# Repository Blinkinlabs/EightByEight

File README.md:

# EightByEight Blinky Badge

EightByEight Blinky Badge, Copyright 2016 Blinkinlabs, LLC

See the ['Getting Started Guide'](https://github.com/Blinkinlabs/EightByEight/blob/master/documentation/Getting%20started%20guide.pdf) in documentation/ to learn about the badge.

Arduino examples are located in examples/.

# License

The hardware design is released under the CERN OHL v.1.2

The firmware and bootloader are released under the MIT license

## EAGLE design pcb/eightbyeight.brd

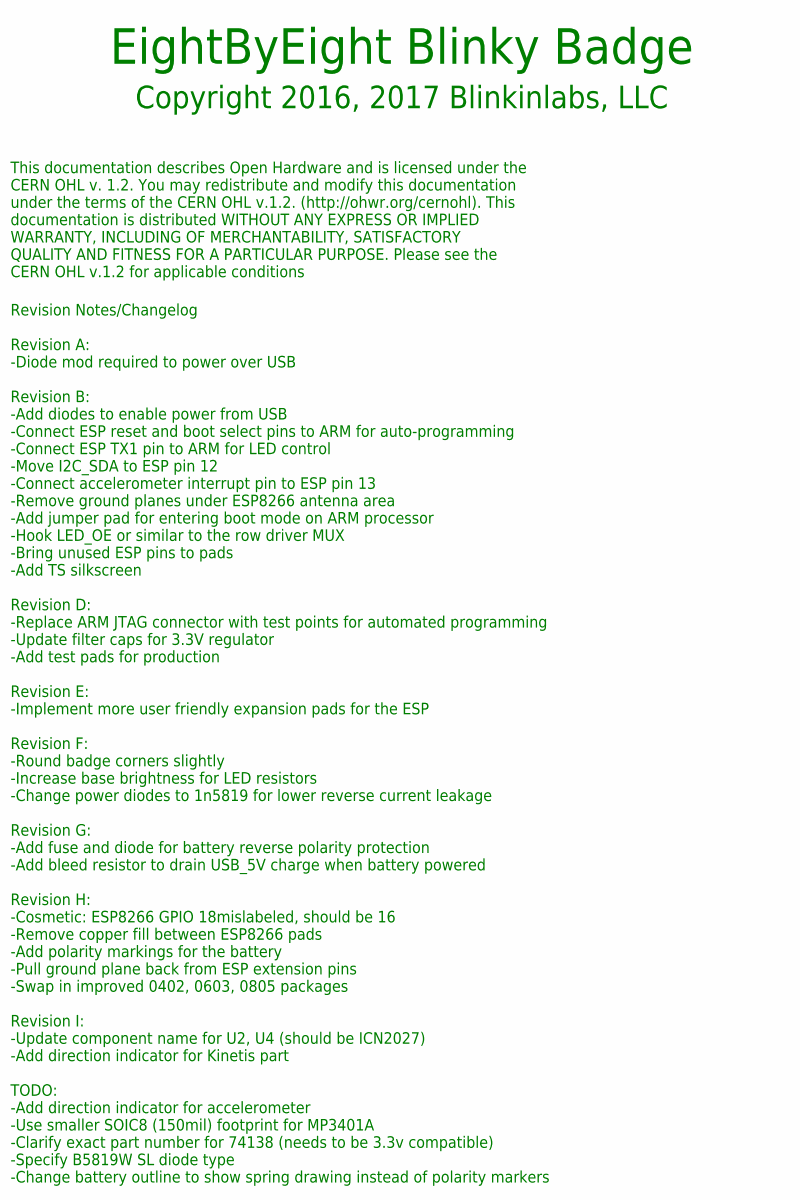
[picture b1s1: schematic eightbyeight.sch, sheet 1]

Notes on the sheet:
Revision Notes/Changelog Revision A: -Diode mod required to power over USB Revision B: -Add diodes to enable power from USB -Connect ESP reset and boot select pins to ARM for auto-programming -Connect ESP TX1 pin to ARM for LED control -Move I2C_SDA to ESP pin 12 -Connect accelerometer interrupt pi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
EightByEight Blinky Badge
Copyright 2016, 2017 Blinkinlabs, LLC
This documentation describes Open Hardware and is licensed under the CERN OHL v. 1.2. You may redistribute and modify this documentation under the terms of the CERN OHL v.1.2. (http://ohwr.org/cernohl). This documentation is distributed WITHOUT ANY EXPRESS OR IMPLIED WARRANTY, INCLUDING OF MERCHANT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

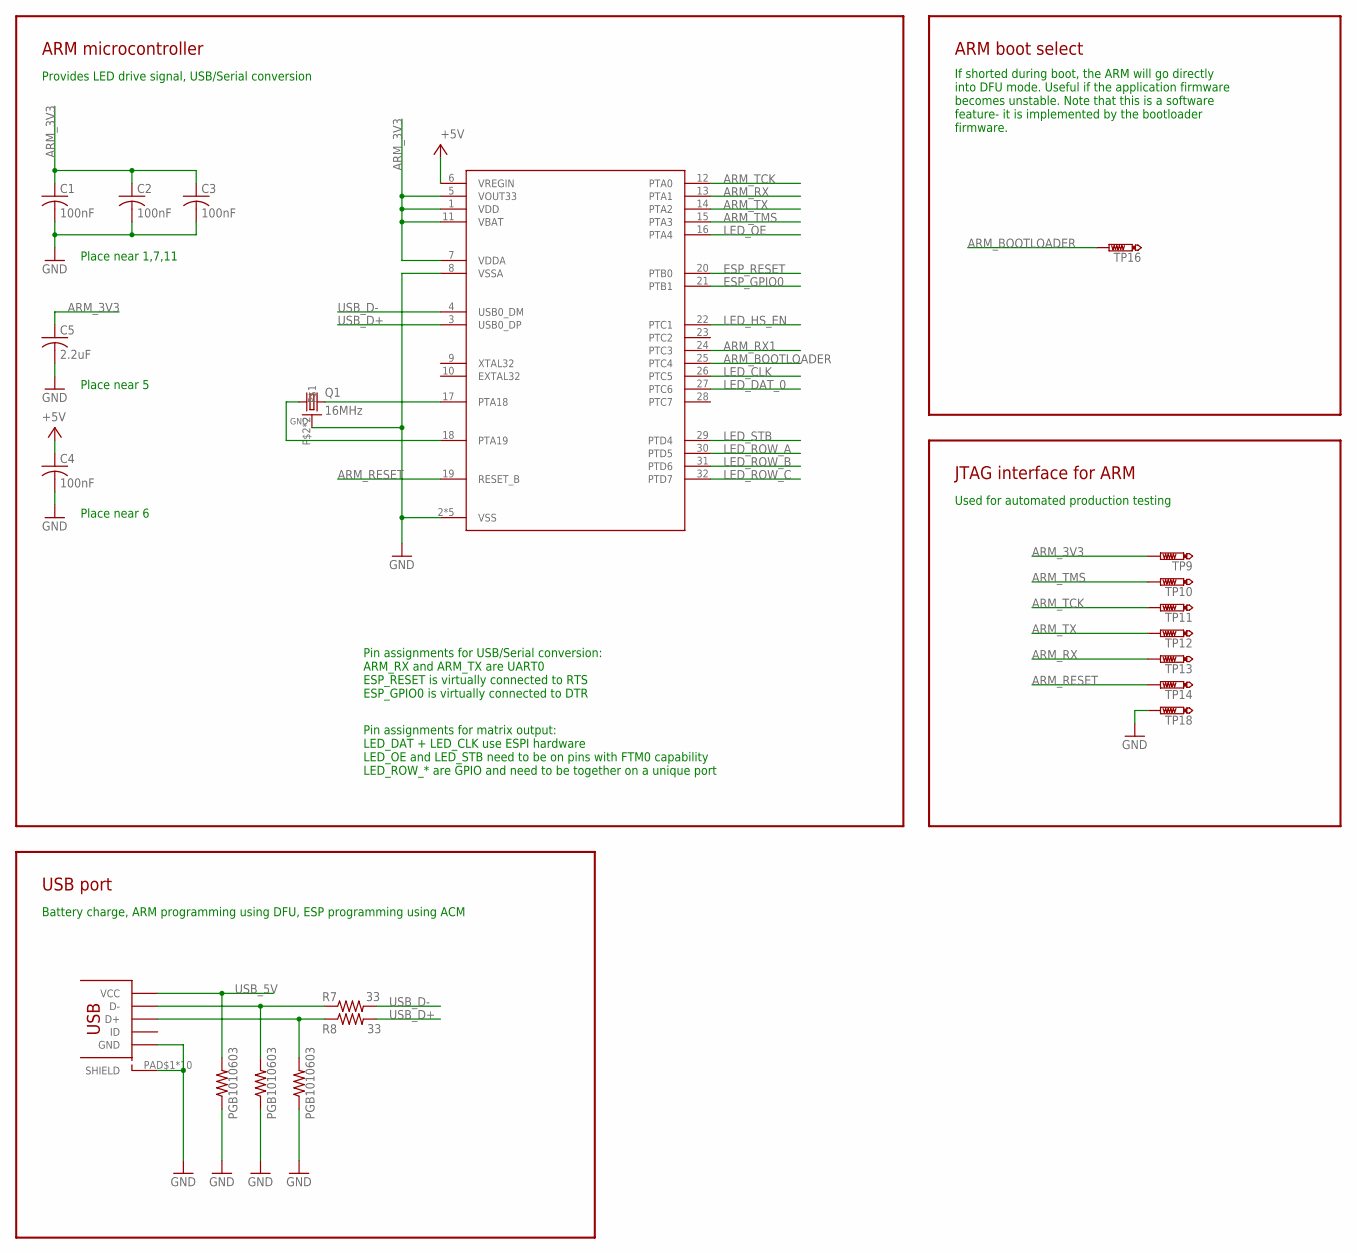
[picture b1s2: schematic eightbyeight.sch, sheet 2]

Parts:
C1, C2, C3, C4: 100nF; CAP_0402
C5: 2.2uF; CAP_0402
J1: USB_MICROSMT+THRUHULE; USB_MICRO_THRUHOLE
Q1: 16MHz; CRSYTAL_2520
R7, R8: 33; R_0402
TP9, TP10, TP11, TP12, TP13, TP14, TP16, TP18: PTR1B1,27; B1,27
U1: MK20DN64VFM5; QFN32_5X5_LONGLEADS
Z1, Z2, Z3: PGB1010603; SPARKFUN-RESISTORS_0603-RES; MPN PGB1010603NRHF

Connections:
+5V: C4.1, U1.6 (VREGIN); also elsewhere on the board
ARM_3V3: C1.1, C2.1, C3.1, C5.1, TP9.TP, U1.1 (VDD), U1.5 (VOUT33), U1.7 (VDDA), U1.11 (VBAT); also elsewhere on the board
ARM_BOOTLOADER: TP16.TP, U1.25 (PTC4)
ARM_RESET: TP14.TP, U1.19 (RESET_B)
ARM_RX: TP13.TP, U1.13 (PTA1); also elsewhere on the board
ARM_RX1: U1.24 (PTC3); also elsewhere on the board
ARM_TCK: TP11.TP, U1.12 (PTA0)
ARM_TMS: TP10.TP, U1.15 (PTA3)
ARM_TX: TP12.TP, U1.14 (PTA2); also elsewhere on the board
ESP_GPIO0: U1.21 (PTB1); also elsewhere on the board
ESP_RESET: U1.20 (PTB0); also elsewhere on the board
GND: C1.2, C2.2, C3.2, C4.2, C5.2, J1.PAD$1 (SHIELD), J1.PAD$2 (SHIELD), J1.PAD$3 (SHIELD), J1.PAD$4 (SHIELD), J1.PAD$5 (SHIELD), J1.PAD$6 (SHIELD), J1.PAD$7 (SHIELD), J1.PAD$8 (SHIELD), J1.PAD$9 (SHIELD), J1.PAD$10 (SHIELD), J1.PIN$5 (GND), Q1.P$2, Q1.P$4, TP18.TP, U1.2 (VSS), U1.8 (VSSA), U1.PAD@1 (VSS), U1.PAD@4 (VSS), U1.PAD@9 (VSS), U1.PAD@11 (VSS), Z1.1, Z2.1, Z3.1; also elsewhere on the board
LED_CLK: U1.26 (PTC5); also elsewhere on the board
LED_DAT_0: U1.27 (PTC6); also elsewhere on the board
LED_HS_EN: U1.22 (PTC1); also elsewhere on the board
LED_OE: U1.16 (PTA4); also elsewhere on the board
LED_ROW_A: U1.30 (PTD5); also elsewhere on the board
LED_ROW_B: U1.31 (PTD6); also elsewhere on the board
LED_ROW_C: U1.32 (PTD7); also elsewhere on the board
LED_STB: U1.29 (PTD4); also elsewhere on the board
unnamed: Q1.P$3 (2), U1.17 (PTA18)
unnamed: J1.PIN$2 (D-), R7.1, Z1.2
unnamed: J1.PIN$3 (D+), R8.1, Z2.2
unnamed: Q1.P$1 (1), U1.18 (PTA19)
USB_5V: J1.PIN$1 (VCC), Z3.2; also elsewhere on the board
USB_D+: R8.2, U1.3 (USB0_DP)
USB_D-: R7.2, U1.4 (USB0_DM)

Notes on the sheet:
Pin assignments for matrix output: LED_DAT + LED_CLK use ESPI hardware LED_OE and LED_STB need to be on pins with FTM0 capability LED_ROW_* are GPIO and need to be together on a unique port
Provides LED drive signal, USB/Serial conversion
ARM microcontroller
Place near 1,7,11
Place near 5
Place near 6
Battery charge, ARM programming using DFU, ESP programming using ACM
USB port
Pin assignments for USB/Serial conversion: ARM_RX and ARM_TX are UART0 ESP_RESET is virtually connected to RTS ESP_GPIO0 is virtually connected to DTR
If shorted during boot, the ARM will go directly into DFU mode. Useful if the application firmware becomes unstable. Note that this is a software feature- it is implemented by the bootloader firmware.
ARM boot select
Used for automated production testing
JTAG interface for ARM

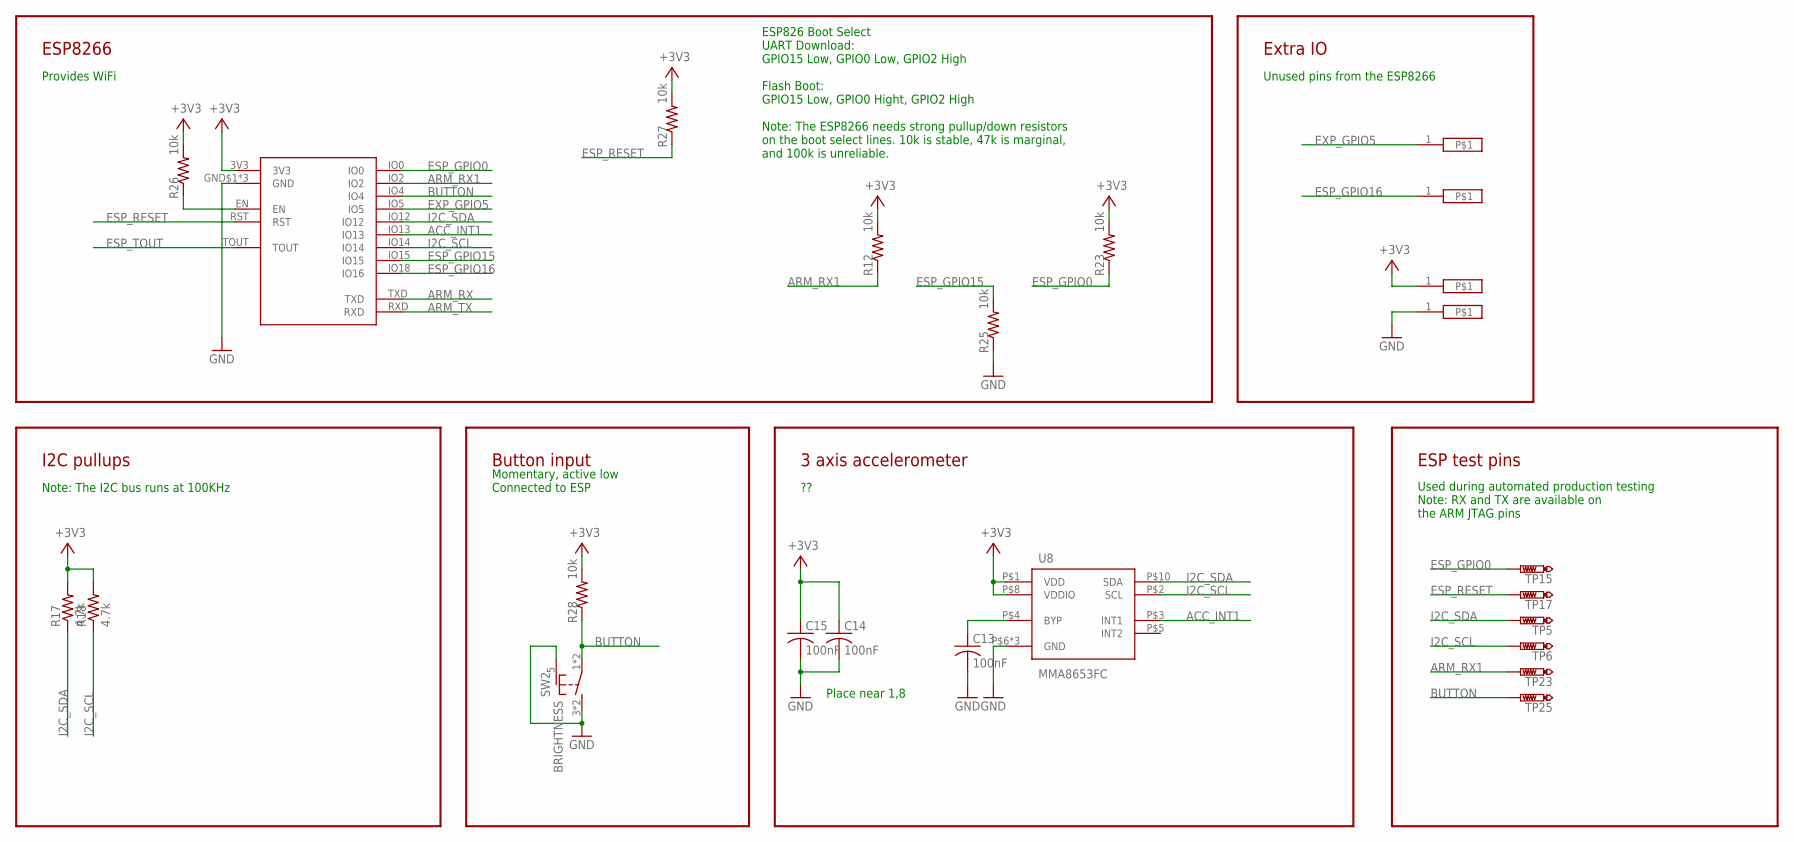
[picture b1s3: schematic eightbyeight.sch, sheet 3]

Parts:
C13, C14, C15: 100nF; CAP_0402
R12, R23, R25, R26, R27, R28: 10k; R_0402
R17, R18: 4.7k; R_0402
SW2: BRIGHTNESS; TD-07XB
TP5, TP6, TP15, TP17, TP23, TP25: PTR1B1,27; B1,27
U6: ESP_WROOM_02
U8: MMA8653FC; VFDFN-10
U$2, U$6, U$9, U$10: TEST_POINT; IO_HOLE_3MM

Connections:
+3V3: C14.1, C15.1, R12.2, R17.2, R18.2, R23.2, R26.2, R27.2, R28.2, U6.3V3, U8.P$1 (VDD), U8.P$8 (VDDIO), U$10.1; also elsewhere on the board
ACC_INT1: U6.IO13, U8.P$3 (INT1)
ARM_RX: U6.TXD; also elsewhere on the board
ARM_RX1: R12.1, TP23.TP, U6.IO2; also elsewhere on the board
ARM_TX: U6.RXD; also elsewhere on the board
BUTTON: R28.1, SW2.1, SW2.2, TP25.TP, U6.IO4
ESP_ENABLE: R26.1, U6.EN
ESP_GPIO0: R23.1, TP15.TP, U6.IO0; also elsewhere on the board
ESP_GPIO15: R25.2, U6.IO15
ESP_GPIO16: U6.IO18 (IO16), U$9.1
ESP_RESET: R27.1, TP17.TP, U6.RST; also elsewhere on the board
ESP_TOUT: U6.TOUT
EXP_GPIO5: U6.IO5, U$6.1
GND: C13.2, C14.2, C15.2, R25.1, SW2.3 (S), SW2.4 (S), SW2.5 (SHIELD), U6.GND$1 (GND), U6.GND$2 (GND), U6.GND$3 (GND), U8.P$6 (GND), U8.P$7 (GND), U8.P$9 (GND), U$2.1; also elsewhere on the board
I2C_SCL: R18.1, TP6.TP, U6.IO14, U8.P$2 (SCL)
I2C_SDA: R17.1, TP5.TP, U6.IO12, U8.P$10 (SDA)
unnamed: C13.1, U8.P$4 (BYP)

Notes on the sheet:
Provides WiFi
ESP8266
ESP826 Boot Select UART Download: GPIO15 Low, GPIO0 Low, GPIO2 High Flash Boot: GPIO15 Low, GPIO0 Hight, GPIO2 High Note: The ESP8266 needs strong pullup/down resistors on the boot select lines. 10k is stable, 47k is marginal, and 100k is unreliable.
Note: The I2C bus runs at 100KHz
I2C pullups
Momentary, active low Connected to ESP
Button input
3 axis accelerometer
Place near 1,8
Unused pins from the ESP8266
Extra IO
Used during automated production testing Note: RX and TX are available on the ARM JTAG pins
ESP test pins

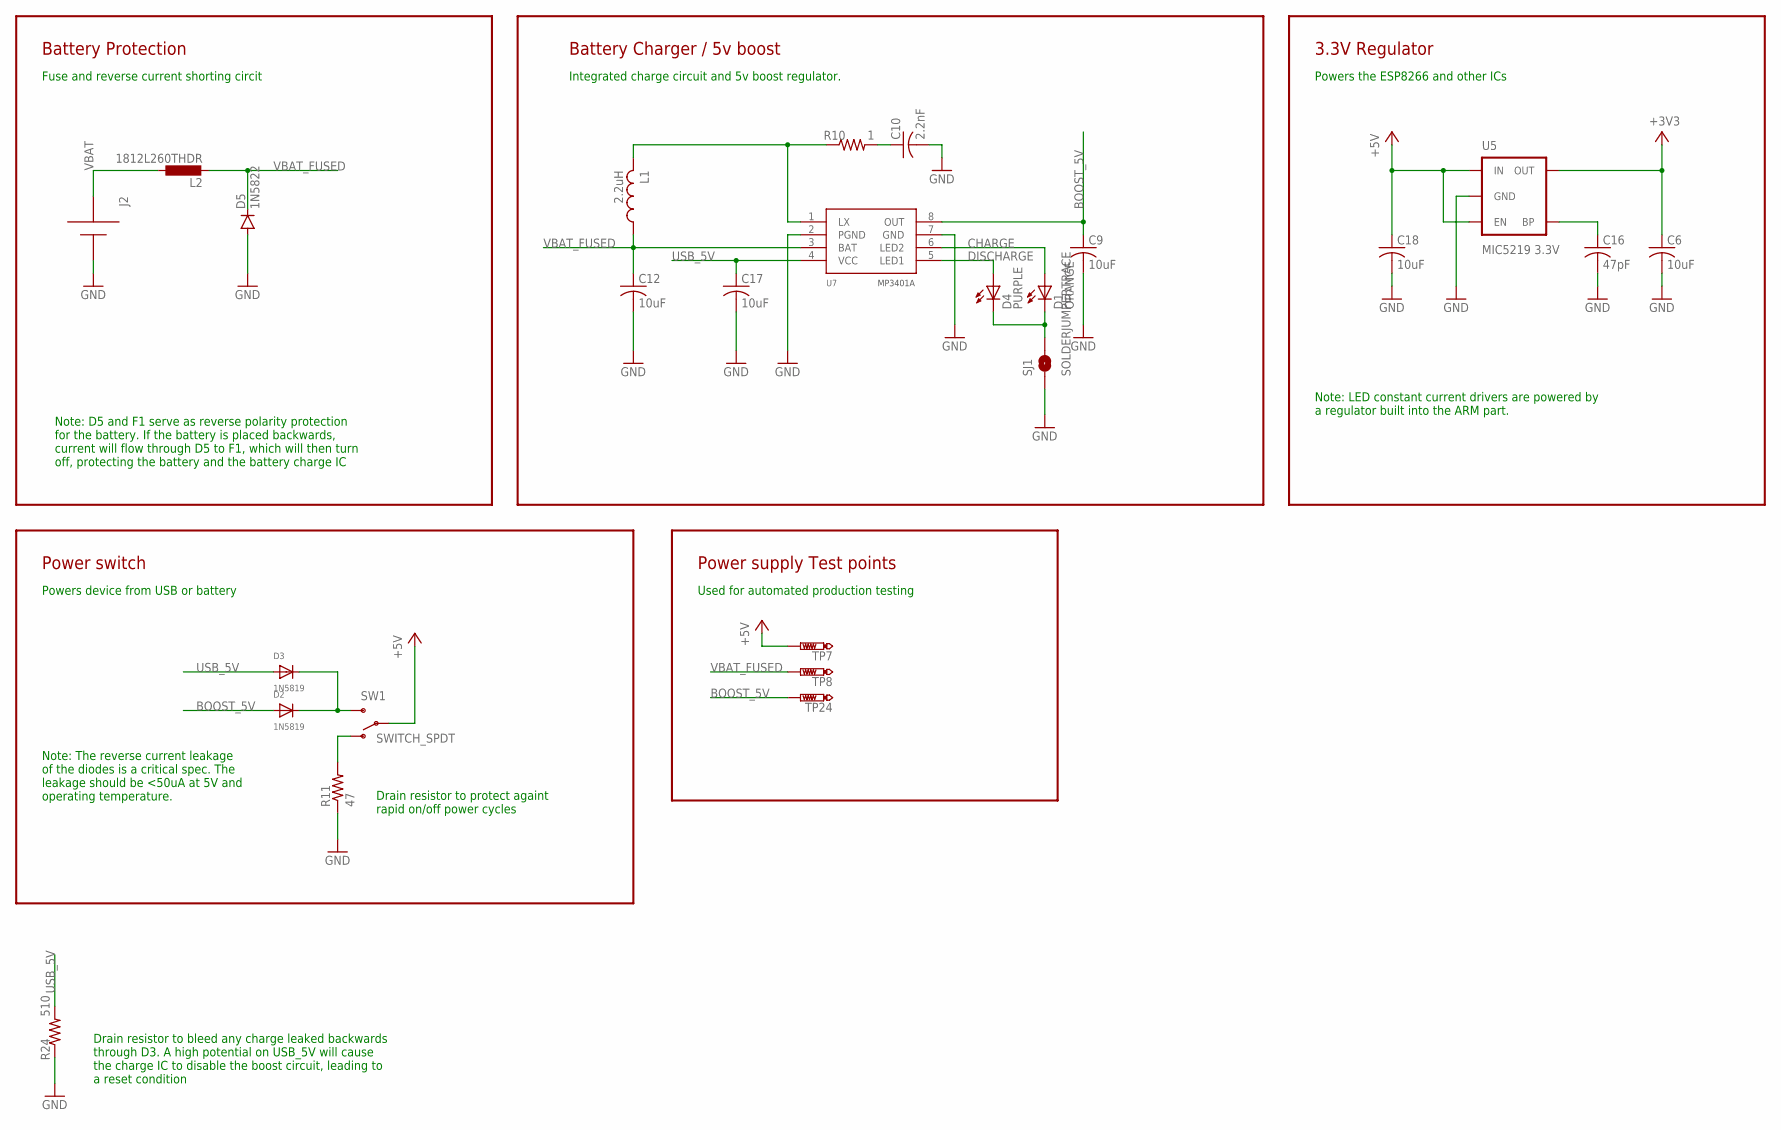
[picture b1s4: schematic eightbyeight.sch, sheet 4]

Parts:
C6, C9, C12, C17, C18: 10uF; CAP_0805
C10: 2.2nF; CAP_0603
C16: 47pF; CAP_0402
D1: ORANGE; CHIP-LED0603
D2, D3: 1N5819; SOD-123
D4: PURPLE; CHIP-LED0603
D5: 1N5822; SMA-DIODE
J2: BATTERYAA_SMD; BATTERY_AA_SMD
L1: 2.2uH; INDUCTOR_CD43
L2: 1812L260THDR; L1812
R10: 1; R_0603
R11: 47; R_0805
R24: 510; R_0603
SJ1: SOLDERJUMPERTRACE; SJ_2S-TRACE
SW1: SWITCH_SPDT; SWITCH_6P-2POS
TP7, TP8, TP24: PTR1B1,27; B1,27
U5: MIC5219 3.3V; SOT23-5
U7: MP3401A; SO08-150

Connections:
+3V3: C6.1, U5.5 (OUT); also elsewhere on the board
+5V: C18.1, SW1.P0, SW1.P1, TP7.TP, U5.1 (IN), U5.3 (EN); also elsewhere on the board
+5V_BLEED: R11.2, SW1.O0 (O), SW1.O1 (O)
+5V_SWITCH: D2.C, D3.C, SW1.S0 (S), SW1.S1 (S)
BOOST_5V: C9.1, D2.A, TP24.TP, U7.8 (OUT)
CHARGE: D1.A, U7.6 (LED2)
DISCHARGE: D4.A, U7.5 (LED1)
GND: C6.2, C9.2, C10.2, C12.2, C16.2, C17.2, C18.2, D5.A, J2.-, R11.1, R24.1, SJ1.1, U5.2 (GND), U7.2 (PGND), U7.7 (GND); also elsewhere on the board
unnamed: D1.C, D4.C, SJ1.2
unnamed: L1.P$2 (2), R10.1, U7.1 (LX)
unnamed: C10.1, R10.2
unnamed: C16.1, U5.4 (BP)
USB_5V: C17.1, D3.A, R24.2, U7.4 (VCC); also elsewhere on the board
VBAT: J2.+, L2.1
VBAT_FUSED: C12.1, D5.C, L1.P$1 (1), L2.2, TP8.TP, U7.3 (BAT)

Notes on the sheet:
Fuse and reverse current shorting circit
Battery Protection
Powers the ESP8266 and other ICs
3.3V Regulator
Note: LED constant current drivers are powered by a regulator built into the ARM part.
Drain resistor to protect againt rapid on/off power cycles
Powers device from USB or battery
Power switch
Used for automated production testing
Power supply Test points
Note: D5 and F1 serve as reverse polarity protection for the battery. If the battery is placed backwards, current will flow through D5 to F1, which will then turn off, protecting the battery and the battery charge IC
Integrated charge circuit and 5v boost regulator.
Battery Charger / 5v boost
Drain resistor to bleed any charge leaked backwards through D3. A high potential on USB_5V will cause the charge IC to disable the boost circuit, leading to a reset condition
Note: The reverse current leakage of the diodes is a critical spec. The leakage should be <50uA at 5V and operating temperature.

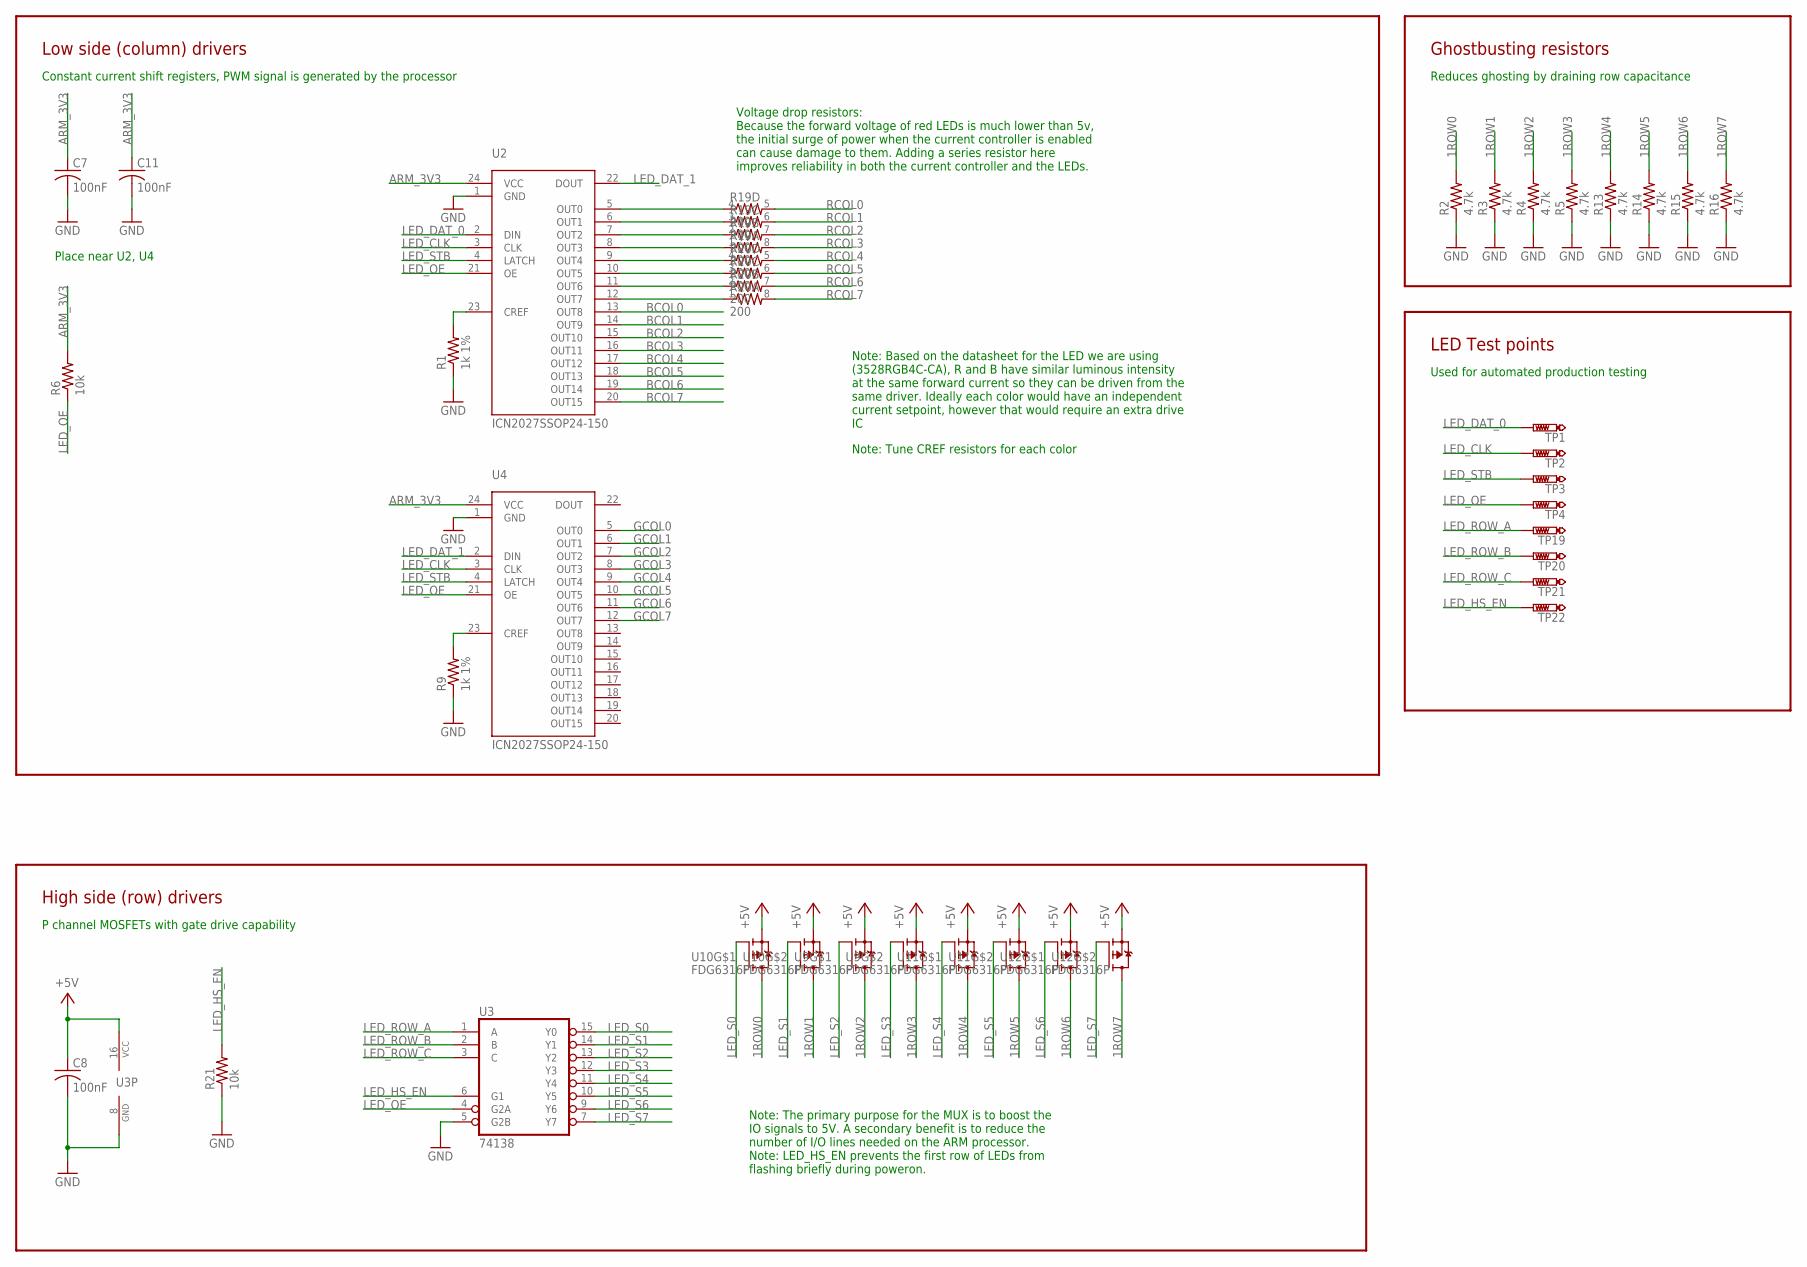
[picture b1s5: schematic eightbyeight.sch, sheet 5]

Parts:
C7, C8, C11: 100nF; CAP_0402
R1, R9: 1k 1%; R_0402
R2, R3, R4, R5, R13, R14, R15, R16: 4.7k; R_0402
R6, R21: 10k; R_0402
R19, R20: 200; 0603-ARV
TP1, TP2, TP3, TP4, TP19, TP20, TP21, TP22: PTR1B1,27; B1,27
U2, U4: ICN2027SSOP24-150; SSOP24-150
U3: 74138; TSSOP16
U9, U10, U11, U12: FDG6316P; SC70-6L

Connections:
1ROW0: R2.2, U10.6 (D); also elsewhere on the board
1ROW1: R3.2, U10.3 (D); also elsewhere on the board
1ROW2: R4.2, U9.6 (D); also elsewhere on the board
1ROW3: R5.2, U9.3 (D); also elsewhere on the board
1ROW4: R13.2, U11.6 (D); also elsewhere on the board
1ROW5: R14.2, U11.3 (D); also elsewhere on the board
1ROW6: R15.2, U12.6 (D); also elsewhere on the board
1ROW7: R16.2, U12.3 (D); also elsewhere on the board
+5V: C8.1, U3.16 (VCC), U9.1 (S), U9.4 (S), U10.1 (S), U10.4 (S), U11.1 (S), U11.4 (S), U12.1 (S), U12.4 (S); also elsewhere on the board
ARM_3V3: C7.1, C11.1, R6.2, U2.24 (VCC), U4.24 (VCC); also elsewhere on the board
BCOL0: U2.13 (OUT8); also elsewhere on the board
BCOL1: U2.14 (OUT9); also elsewhere on the board
BCOL2: U2.15 (OUT10); also elsewhere on the board
BCOL3: U2.16 (OUT11); also elsewhere on the board
BCOL4: U2.17 (OUT12); also elsewhere on the board
BCOL5: U2.18 (OUT13); also elsewhere on the board
BCOL6: U2.19 (OUT14); also elsewhere on the board
BCOL7: U2.20 (OUT15); also elsewhere on the board
GCOL0: U4.5 (OUT0); also elsewhere on the board
GCOL1: U4.6 (OUT1); also elsewhere on the board
GCOL2: U4.7 (OUT2); also elsewhere on the board
GCOL3: U4.8 (OUT3); also elsewhere on the board
GCOL4: U4.9 (OUT4); also elsewhere on the board
GCOL5: U4.10 (OUT5); also elsewhere on the board
GCOL6: U4.11 (OUT6); also elsewhere on the board
GCOL7: U4.12 (OUT7); also elsewhere on the board
GND: C7.2, C8.2, C11.2, R1.1, R2.1, R3.1, R4.1, R5.1, R9.1, R13.1, R14.1, R15.1, R16.1, R21.1, U2.1 (GND), U3.5 (G2B), U3.8 (GND), U4.1 (GND); also elsewhere on the board
LED_CLK: TP2.TP, U2.3 (CLK), U4.3 (CLK); also elsewhere on the board
LED_DAT_0: TP1.TP, U2.2 (DIN); also elsewhere on the board
LED_DAT_1: U2.22 (DOUT), U4.2 (DIN)
LED_HS_EN: R21.2, TP22.TP, U3.6 (G1); also elsewhere on the board
LED_OE: R6.1, TP4.TP, U2.21 (OE), U3.4 (G2A), U4.21 (OE); also elsewhere on the board
LED_ROW_A: TP19.TP, U3.1 (A); also elsewhere on the board
LED_ROW_B: TP20.TP, U3.2 (B); also elsewhere on the board
LED_ROW_C: TP21.TP, U3.3 (C); also elsewhere on the board
LED_S0: U3.15 (Y0), U10.2 (G)
LED_S1: U3.14 (Y1), U10.5 (G)
LED_S2: U3.13 (Y2), U9.2 (G)
LED_S3: U3.12 (Y3), U9.5 (G)
LED_S4: U3.11 (Y4), U11.2 (G)
LED_S5: U3.10 (Y5), U11.5 (G)
LED_S6: U3.9 (Y6), U12.2 (G)
LED_S7: U3.7 (Y7), U12.5 (G)
LED_STB: TP3.TP, U2.4 (LATCH), U4.4 (LATCH); also elsewhere on the board
unnamed: R9.2, U4.23 (CREF)
unnamed: R1.2, U2.23 (CREF)
RCOL0: R19.5 (2); also elsewhere on the board
RCOL0_: R19.4 (1), U2.5 (OUT0)
RCOL1: R19.6 (2); also elsewhere on the board
RCOL1_: R19.3 (1), U2.6 (OUT1)
RCOL2: R19.7 (2); also elsewhere on the board
RCOL2_: R19.2 (1), U2.7 (OUT2)
RCOL3: R19.8 (2); also elsewhere on the board
RCOL3_: R19.1, U2.8 (OUT3)
RCOL4: R20.5 (2); also elsewhere on the board
RCOL4_: R20.4 (1), U2.9 (OUT4)
RCOL5: R20.6 (2); also elsewhere on the board
RCOL5_: R20.3 (1), U2.10 (OUT5)
RCOL6: R20.7 (2); also elsewhere on the board
RCOL6_: R20.2 (1), U2.11 (OUT6)
RCOL7: R20.8 (2); also elsewhere on the board
RCOL7_: R20.1, U2.12 (OUT7)

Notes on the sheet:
Constant current shift registers, PWM signal is generated by the processor
Low side (column) drivers
Note: Tune CREF resistors for each color
Place near U2, U4
P channel MOSFETs with gate drive capability
High side (row) drivers
Reduces ghosting by draining row capacitance
Ghostbusting resistors
Voltage drop resistors: Because the forward voltage of red LEDs is much lower than 5v, the initial surge of power when the current controller is enabled can cause damage to them. Adding a series resistor here improves reliability in both the current controller and the LEDs.
Note: Based on the datasheet for the LED we are using (3528RGB4C-CA), R and B have similar luminous intensity at the same forward current so they can be driven from the same driver. Ideally each color would have an independent current setpoint, however that would require an extra drive IC
Note: The primary purpose for the MUX is to boost the IO signals to 5V. A secondary benefit is to reduce the number of I/O lines needed on the ARM processor. Note: LED_HS_EN prevents the first row of LEDs from flashing briefly during poweron.
Used for automated production testing
LED Test points

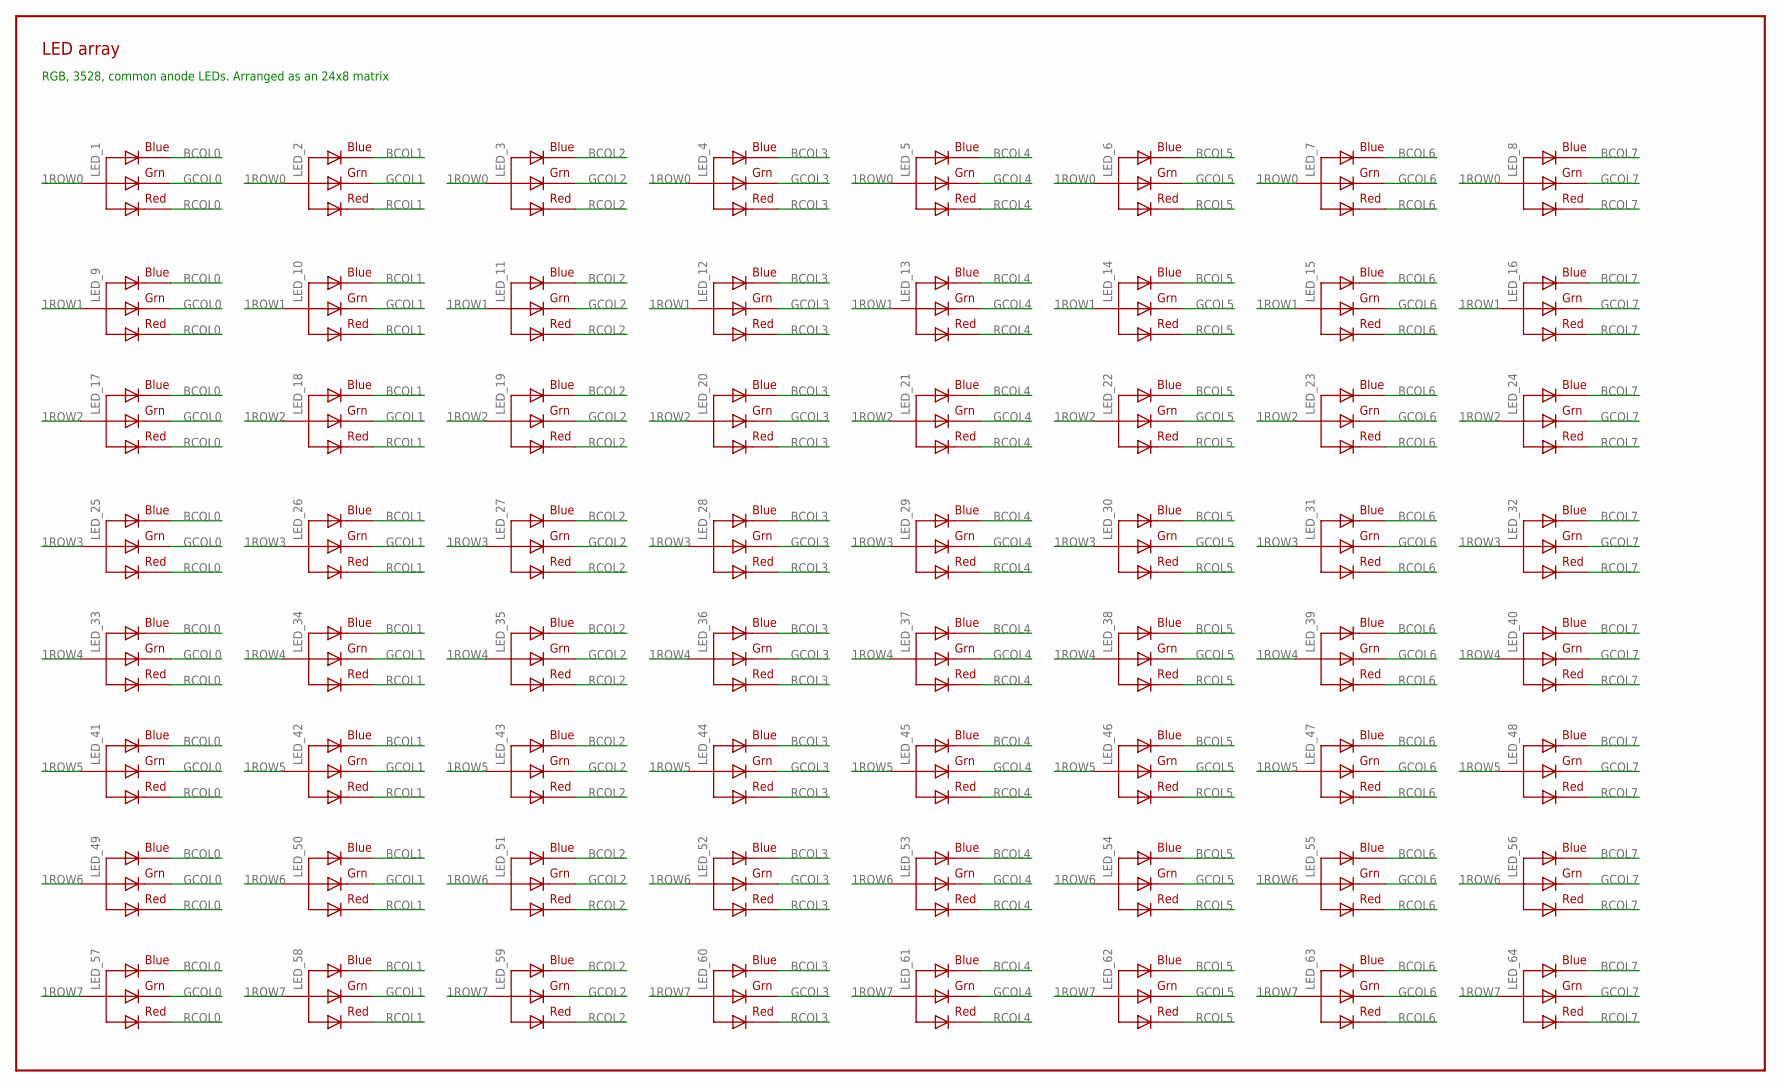
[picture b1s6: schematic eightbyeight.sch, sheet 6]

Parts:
LED_1, LED_2, LED_3, LED_4, LED_5, LED_6, LED_7, LED_8, LED_9, LED_10, LED_11, LED_12, LED_13, LED_14, LED_15, LED_16, LED_17, LED_18, LED_19, LED_20, LED_21, LED_22, LED_23, LED_24, LED_25, LED_26, LED_27, LED_28, LED_29, LED_30, LED_31, LED_32, LED_33, LED_34, LED_35, LED_36, LED_37, LED_38, LED_39, LED_40, LED_41, LED_42, LED_43, LED_44, LED_45, LED_46, LED_47, LED_48, LED_49, LED_50, LED_51, LED_52, LED_53, LED_54, LED_55, LED_56, LED_57, LED_58, LED_59, LED_60, LED_61, LED_62, LED_63, LED_64: LED_RGB_CA3528; LED_3528

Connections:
1ROW0: LED_1.2 (VCC), LED_2.2 (VCC), LED_3.2 (VCC), LED_4.2 (VCC), LED_5.2 (VCC), LED_6.2 (VCC), LED_7.2 (VCC), LED_8.2 (VCC); also elsewhere on the board
1ROW1: LED_9.2 (VCC), LED_10.2 (VCC), LED_11.2 (VCC), LED_12.2 (VCC), LED_13.2 (VCC), LED_14.2 (VCC), LED_15.2 (VCC), LED_16.2 (VCC); also elsewhere on the board
1ROW2: LED_17.2 (VCC), LED_18.2 (VCC), LED_19.2 (VCC), LED_20.2 (VCC), LED_21.2 (VCC), LED_22.2 (VCC), LED_23.2 (VCC), LED_24.2 (VCC); also elsewhere on the board
1ROW3: LED_25.2 (VCC), LED_26.2 (VCC), LED_27.2 (VCC), LED_28.2 (VCC), LED_29.2 (VCC), LED_30.2 (VCC), LED_31.2 (VCC), LED_32.2 (VCC); also elsewhere on the board
1ROW4: LED_33.2 (VCC), LED_34.2 (VCC), LED_35.2 (VCC), LED_36.2 (VCC), LED_37.2 (VCC), LED_38.2 (VCC), LED_39.2 (VCC), LED_40.2 (VCC); also elsewhere on the board
1ROW5: LED_41.2 (VCC), LED_42.2 (VCC), LED_43.2 (VCC), LED_44.2 (VCC), LED_45.2 (VCC), LED_46.2 (VCC), LED_47.2 (VCC), LED_48.2 (VCC); also elsewhere on the board
1ROW6: LED_49.2 (VCC), LED_50.2 (VCC), LED_51.2 (VCC), LED_52.2 (VCC), LED_53.2 (VCC), LED_54.2 (VCC), LED_55.2 (VCC), LED_56.2 (VCC); also elsewhere on the board
1ROW7: LED_57.2 (VCC), LED_58.2 (VCC), LED_59.2 (VCC), LED_60.2 (VCC), LED_61.2 (VCC), LED_62.2 (VCC), LED_63.2 (VCC), LED_64.2 (VCC); also elsewhere on the board
BCOL0: LED_1.3 (BLUE), LED_9.3 (BLUE), LED_17.3 (BLUE), LED_25.3 (BLUE), LED_33.3 (BLUE), LED_41.3 (BLUE), LED_49.3 (BLUE), LED_57.3 (BLUE); also elsewhere on the board
BCOL1: LED_2.3 (BLUE), LED_10.3 (BLUE), LED_18.3 (BLUE), LED_26.3 (BLUE), LED_34.3 (BLUE), LED_42.3 (BLUE), LED_50.3 (BLUE), LED_58.3 (BLUE); also elsewhere on the board
BCOL2: LED_3.3 (BLUE), LED_11.3 (BLUE), LED_19.3 (BLUE), LED_27.3 (BLUE), LED_35.3 (BLUE), LED_43.3 (BLUE), LED_51.3 (BLUE), LED_59.3 (BLUE); also elsewhere on the board
BCOL3: LED_4.3 (BLUE), LED_12.3 (BLUE), LED_20.3 (BLUE), LED_28.3 (BLUE), LED_36.3 (BLUE), LED_44.3 (BLUE), LED_52.3 (BLUE), LED_60.3 (BLUE); also elsewhere on the board
BCOL4: LED_5.3 (BLUE), LED_13.3 (BLUE), LED_21.3 (BLUE), LED_29.3 (BLUE), LED_37.3 (BLUE), LED_45.3 (BLUE), LED_53.3 (BLUE), LED_61.3 (BLUE); also elsewhere on the board
BCOL5: LED_6.3 (BLUE), LED_14.3 (BLUE), LED_22.3 (BLUE), LED_30.3 (BLUE), LED_38.3 (BLUE), LED_46.3 (BLUE), LED_54.3 (BLUE), LED_62.3 (BLUE); also elsewhere on the board
BCOL6: LED_7.3 (BLUE), LED_15.3 (BLUE), LED_23.3 (BLUE), LED_31.3 (BLUE), LED_39.3 (BLUE), LED_47.3 (BLUE), LED_55.3 (BLUE), LED_63.3 (BLUE); also elsewhere on the board
BCOL7: LED_8.3 (BLUE), LED_16.3 (BLUE), LED_24.3 (BLUE), LED_32.3 (BLUE), LED_40.3 (BLUE), LED_48.3 (BLUE), LED_56.3 (BLUE), LED_64.3 (BLUE); also elsewhere on the board
GCOL0: LED_1.4 (GREEN), LED_9.4 (GREEN), LED_17.4 (GREEN), LED_25.4 (GREEN), LED_33.4 (GREEN), LED_41.4 (GREEN), LED_49.4 (GREEN), LED_57.4 (GREEN); also elsewhere on the board
GCOL1: LED_2.4 (GREEN), LED_10.4 (GREEN), LED_18.4 (GREEN), LED_26.4 (GREEN), LED_34.4 (GREEN), LED_42.4 (GREEN), LED_50.4 (GREEN), LED_58.4 (GREEN); also elsewhere on the board
GCOL2: LED_3.4 (GREEN), LED_11.4 (GREEN), LED_19.4 (GREEN), LED_27.4 (GREEN), LED_35.4 (GREEN), LED_43.4 (GREEN), LED_51.4 (GREEN), LED_59.4 (GREEN); also elsewhere on the board
GCOL3: LED_4.4 (GREEN), LED_12.4 (GREEN), LED_20.4 (GREEN), LED_28.4 (GREEN), LED_36.4 (GREEN), LED_44.4 (GREEN), LED_52.4 (GREEN), LED_60.4 (GREEN); also elsewhere on the board
GCOL4: LED_5.4 (GREEN), LED_13.4 (GREEN), LED_21.4 (GREEN), LED_29.4 (GREEN), LED_37.4 (GREEN), LED_45.4 (GREEN), LED_53.4 (GREEN), LED_61.4 (GREEN); also elsewhere on the board
GCOL5: LED_6.4 (GREEN), LED_14.4 (GREEN), LED_22.4 (GREEN), LED_30.4 (GREEN), LED_38.4 (GREEN), LED_46.4 (GREEN), LED_54.4 (GREEN), LED_62.4 (GREEN); also elsewhere on the board
GCOL6: LED_7.4 (GREEN), LED_15.4 (GREEN), LED_23.4 (GREEN), LED_31.4 (GREEN), LED_39.4 (GREEN), LED_47.4 (GREEN), LED_55.4 (GREEN), LED_63.4 (GREEN); also elsewhere on the board
GCOL7: LED_8.4 (GREEN), LED_16.4 (GREEN), LED_24.4 (GREEN), LED_32.4 (GREEN), LED_40.4 (GREEN), LED_48.4 (GREEN), LED_56.4 (GREEN), LED_64.4 (GREEN); also elsewhere on the board
RCOL0: LED_1.1 (RED), LED_9.1 (RED), LED_17.1 (RED), LED_25.1 (RED), LED_33.1 (RED), LED_41.1 (RED), LED_49.1 (RED), LED_57.1 (RED); also elsewhere on the board
RCOL1: LED_2.1 (RED), LED_10.1 (RED), LED_18.1 (RED), LED_26.1 (RED), LED_34.1 (RED), LED_42.1 (RED), LED_50.1 (RED), LED_58.1 (RED); also elsewhere on the board
RCOL2: LED_3.1 (RED), LED_11.1 (RED), LED_19.1 (RED), LED_27.1 (RED), LED_35.1 (RED), LED_43.1 (RED), LED_51.1 (RED), LED_59.1 (RED); also elsewhere on the board
RCOL3: LED_4.1 (RED), LED_12.1 (RED), LED_20.1 (RED), LED_28.1 (RED), LED_36.1 (RED), LED_44.1 (RED), LED_52.1 (RED), LED_60.1 (RED); also elsewhere on the board
RCOL4: LED_5.1 (RED), LED_13.1 (RED), LED_21.1 (RED), LED_29.1 (RED), LED_37.1 (RED), LED_45.1 (RED), LED_53.1 (RED), LED_61.1 (RED); also elsewhere on the board
RCOL5: LED_6.1 (RED), LED_14.1 (RED), LED_22.1 (RED), LED_30.1 (RED), LED_38.1 (RED), LED_46.1 (RED), LED_54.1 (RED), LED_62.1 (RED); also elsewhere on the board
RCOL6: LED_7.1 (RED), LED_15.1 (RED), LED_23.1 (RED), LED_31.1 (RED), LED_39.1 (RED), LED_47.1 (RED), LED_55.1 (RED), LED_63.1 (RED); also elsewhere on the board
RCOL7: LED_8.1 (RED), LED_16.1 (RED), LED_24.1 (RED), LED_32.1 (RED), LED_40.1 (RED), LED_48.1 (RED), LED_56.1 (RED), LED_64.1 (RED); also elsewhere on the board

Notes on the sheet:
RGB, 3528, common anode LEDs. Arranged as an 24x8 matrix
LED array

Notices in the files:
parts and their libraries:
SparkFun-Passives: Licensing: Creative Commons ShareAlike 4.0 International - https://creativecommons.org/licenses/by-sa/4.0
SparkFun-Aesthetics: Licensing: CC v3.0 Share-Alike You are welcome to use this library for commercial purposes.
